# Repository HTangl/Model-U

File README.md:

# Model UD

The Model UD is a USB C breakout board based on the Model U designed by [Crane](https://github.com/Crane1195). It is exactly the same size and footprint as the Model U but integrates a schottky diode directly onto the board and adds the "VSYS" pin. This eliminates the need to add a stand alone diode to your circuit when wiring to a Raspberry Pi Pico. You can simply run a wire directly from the VSYS pin on the model UD to the VSYS pin on the Pico.  

The Model UD is specifically designed for use with DIY rectangle controllers to facilitate the use of USB C to GC cables as well as standard USB C to USB A cables.  

I sell these on my [Etsy shop](https://www.etsy.com/shop/HTangl).  

Here is a wiring guide.  

This repository contains the files necessary to order these boards from [JLCPCB](https://jlcpcb.com/).  
Please be aware that JLC does not have a great track record when it comes to SMT part assembly.  
It is normal to receive 1 to 4 bad boards in every batch.  
There is a guide at the bottom of this page that explains how to test the boards.  

There are also files for a modified version of the board with 3mm mounting holes added if you plan to mount the board with screws. These are the "Model BirdD" files, cuz they kinda look like a Model UD with wings.  

### How to order from JLCPCB ###

1. Download the files from this repository by clicking on "Code" and then on "Download Zip". Unzip the "Model-UD-main.zip" but do not unzip the "Model-UD_panel.zip" folders  

2. From the JLCPCB home page click on "Order now"  

3. On the next page click the "Add gerber file" button and select one of the "Model-UD_panel.zip" files in the "Model-UD JLC Files" folder. For this guide I'm using the 10 piece panel. Keep in mind JLC's minimum order quantity is 5 so since I'm using the 10 piece panel file I will end up with 50 individual breakout boards total.  

4. Change the delivery format to "Panel by Customer" and then input the amount of rows and columns needed, for the 10 piece panel it is 2 columns and 5 rows  

5. Scroll down and turn on the "SMT Assembly" slider, leave everything default and then click "Confirm"  

6. On the next page add the BOM and CPL files from the "Model-UD JLC Files" folder. Then select the "Single Piece" button and then click "NEXT"  

7. On this page just leave everything default and click "NEXT"  

8. The final step will show you a preview of what the boards will look like. It is normal for the parts to be off center and only displayed on one board. JLC will place the parts correctly after you place the order. Also note that if you are ordering less than 50 individual breakout boards you will still be charged for 100 resistors, this is normal and is just a JLC policy. For some small parts they have a minimum quantity. Lastly please do not use the price listed in this picture as a reference, the price shown doesn't include tax or shipping and JLC does change their price from time to time. All you have to do now is click "SAVE TO CART" and then finish the checkout process  

### Testing the boards ###

If you plan to sell these I recommend testing them first.  
To do this you will need a USB C to USB C 3.1 gen 2 cable and a 24 pin USB C breakout board.  
Here are links to the breakout board and cable that I use.  
Breakout: https://amazon.com/dp/B07771CFFM or https://amazon.com/dp/B09L816S5W  
USB Cable: https://amazon.com/dp/B07THFJ1J5  

To test the boards you need a multi-meter with a continuity testing mode.  
Start by connecting the Model UD to the 24 pin breakout.  
Next put one lead of the meter on any pin of the Model UD and then drag the other lead of your meter across every pin on the 24 pin breakout.  
Use the chart below to determine which pins should have continuity.  
If you get continuity on a pin that should not have continuity, such as D+ on the Model UD getting continuity on a GND pin, then the Model UD is broken.  

The pins on the left are the Model UD and the right is the 24 pin breakout.  
Please note that if you'd like to test the diode connected to the VSYS pin you will need a meter with a diode test mode and test between the VSYS and 3V pins, this is generally not needed as the chance of having a bad diode is extremely low.  

5V - VBUS (A4, A9, B4, B9)  
3V - RX1/2+ (A11, B11)  
Gnd - GND and Shield (if applicable) (A1, A12, B1, B12)  
D+ - D+ (Either A6 or B6 you will only get continuity on one)  
D3V - TX1/2+ (A2, B2)

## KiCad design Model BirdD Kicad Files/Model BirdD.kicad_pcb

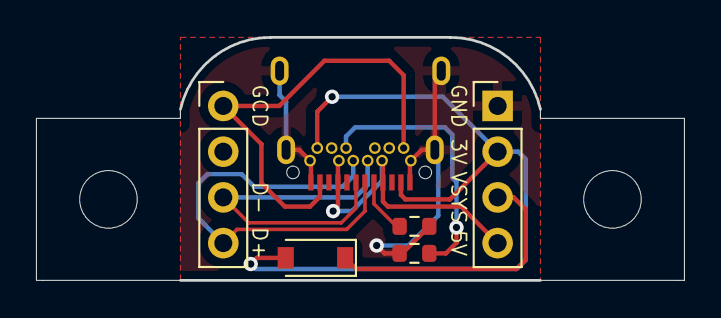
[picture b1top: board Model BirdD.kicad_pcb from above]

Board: 2 copper layers, 35.9 x 13.5 mm, 6 parts (0 on the bottom side), 9 nets.

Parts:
D1: MBR120; D_SOD-123
J1: USB_C_Receptacle; Shou Han Type-C 24P QCHT
J2, J3: Conn_01x04; PinHeader_1x04_P2.54mm_Vertical
R1: 5.1k; R_0603_1608Metric
RE: 5.1k; R_0603_1608Metric

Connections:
3V3: D1.2 (A), J1.A2, J1.B2, J3.2
D3V: J1.A11, J1.B11, J2.1
D+: J1.A6, J1.B6, J2.4
D-: J1.A7, J1.B7, J2.3
GND: J1.A1, J1.A12, J1.B1, J1.B12, J1.S1, J3.1, R1.1, RE.2
unnamed: J1.A5, R1.2
unnamed: J1.B5, RE.1
VBUS: J1.A4, J1.A9, J1.B4, J1.B9, J3.4
VSYS: D1.1 (K), J3.3

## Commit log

2022-01-04 Added JLC files
2022-01-14 Added gerber files for single PCB
2022-04-21 Add Model Bird Files
    Added model bird files along with more pictures and 3D model files
2022-04-21 Add Model Bird Pic
2022-07-11 Change files to Model UD
2022-07-11 Add wiring picture
2022-07-29 Add missing BOM and CPL files
2022-07-29 Remove xml and csv from gitignore
2022-08-22 Add Model BirdD files
2022-08-23 Rename Gerber file
2022-12-19 change wiring and board pictures
2023-01-16 Update wiring picture
